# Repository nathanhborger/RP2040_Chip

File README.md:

# Palette_Chip
All information containing the mini break-out board designed for the RP2040 microcontroller.

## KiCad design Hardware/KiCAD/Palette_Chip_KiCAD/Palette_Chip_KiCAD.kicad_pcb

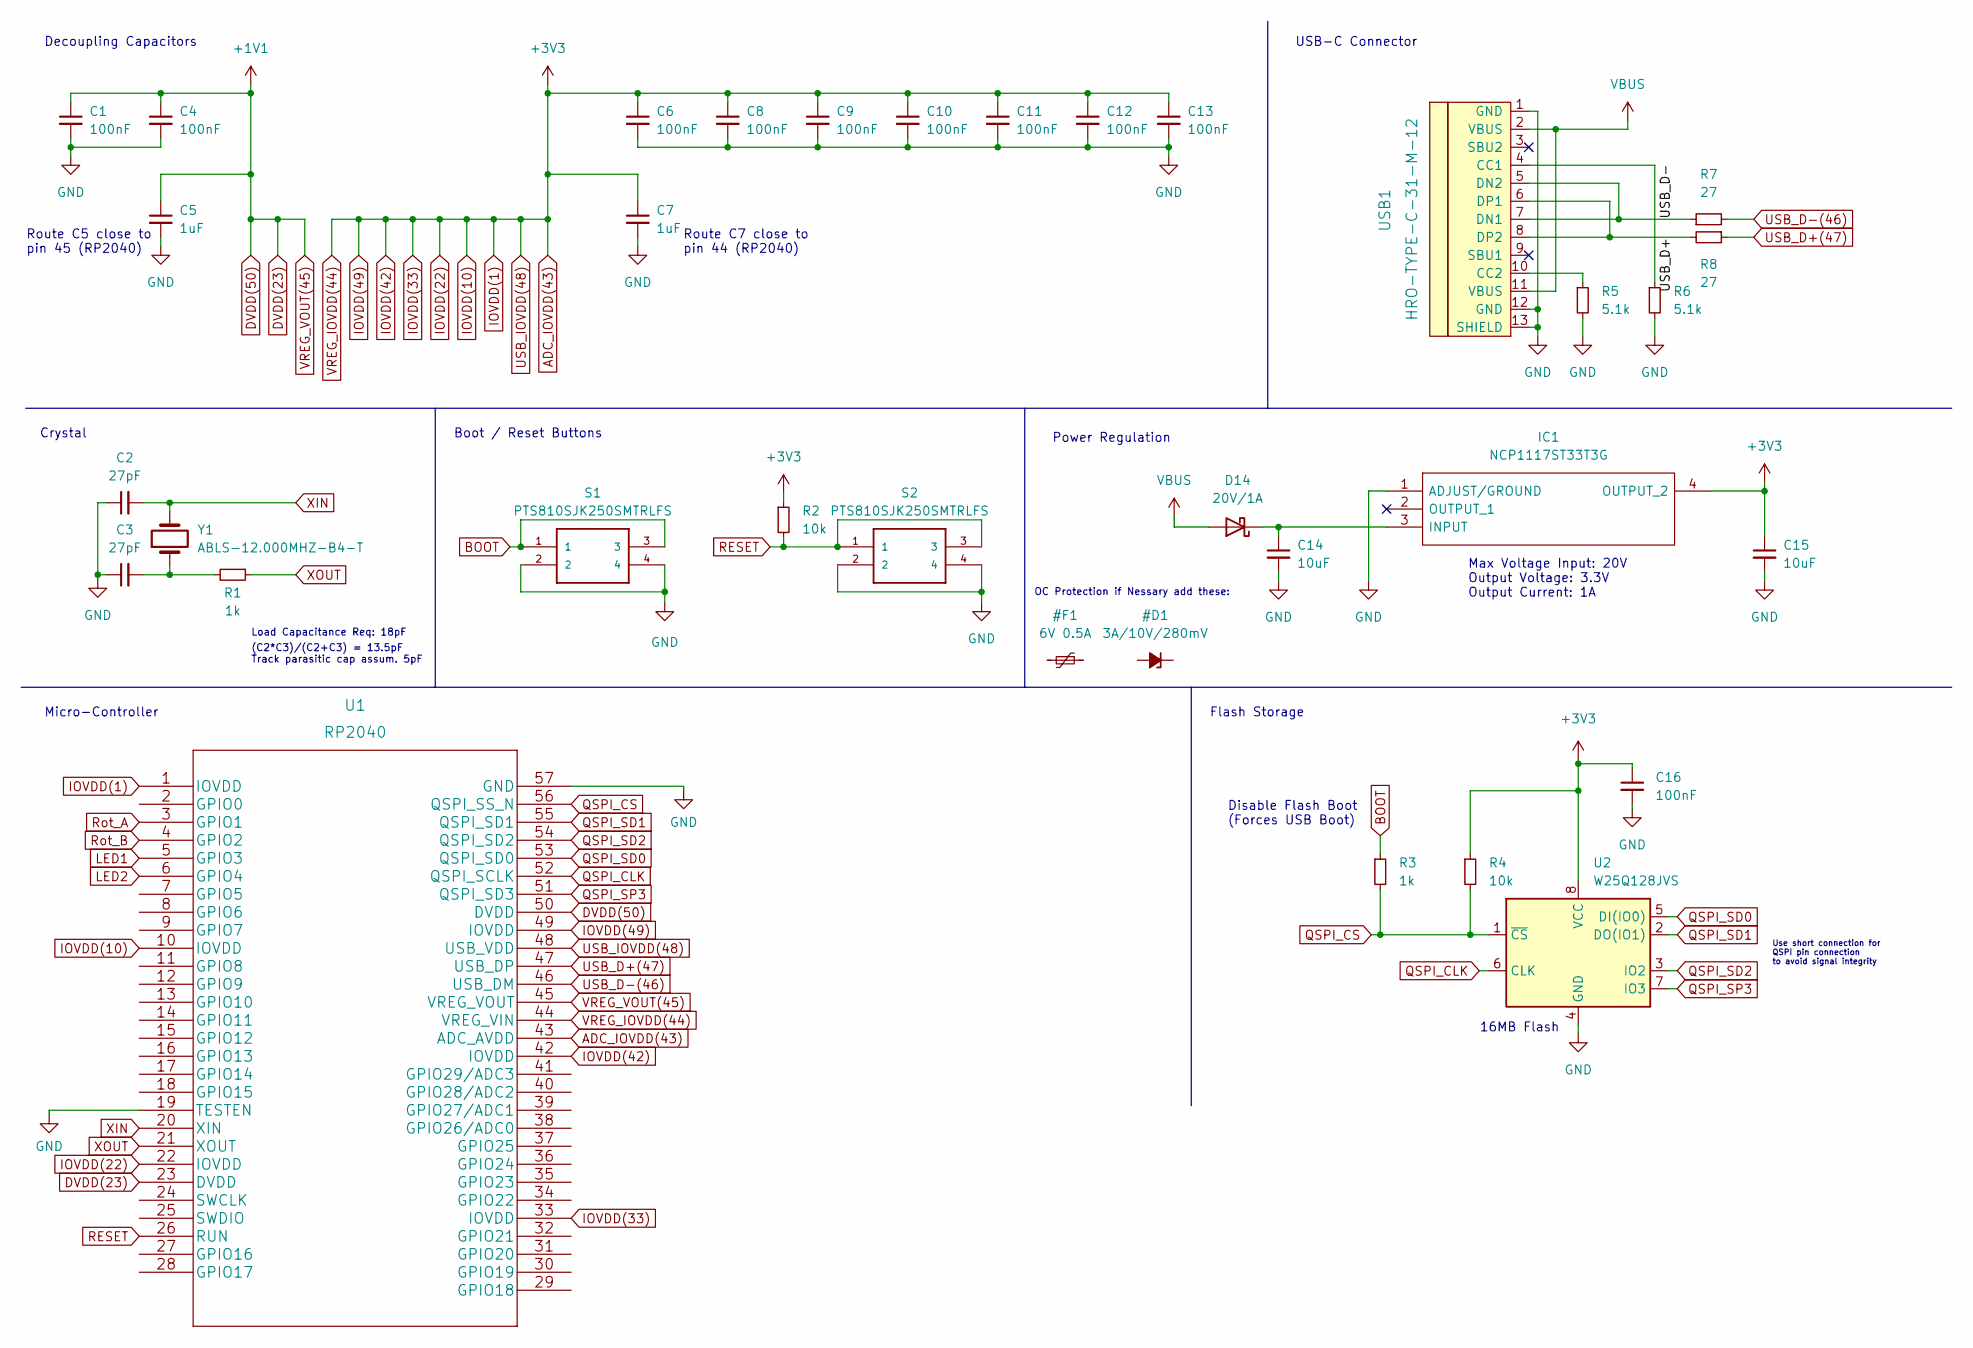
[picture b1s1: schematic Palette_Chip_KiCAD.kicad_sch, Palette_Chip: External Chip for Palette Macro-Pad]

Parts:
C1, C4, C6, C8, C9, C10, C11, C12, C13, C16: 100nF; C_0402_1005Metric
C2, C3: 27pF; C_0402_1005Metric
C5, C7: 1uF; C_0402_1005Metric
C14, C15: 10uF; C_0402_1005Metric
D14: 20V/1A; D_SOD-123F
IC1: NCP1117ST33T3G; SOT230P700X180-4N; Mouser Part Number 863-NCP1117ST33T3G
R1, R3: 1k; R_0402_1005Metric
R2, R4: 10k; R_0402_1005Metric
R5, R6: 5.1k; R_0402_1005Metric
R7, R8: 27; R_0402_1005Metric
S1, S2: PTS810SJK250SMTRLFS; PTS810SJG250SMTRLFS; MANUFACTURER_PART_NUMBER PTS810SJK250SMTRLFS
U1: RP2040; RP2040-QFN-56
U2: W25Q128JVS; SOIC-8_5.23x5.23mm_P1.27mm
USB1: HRO-TYPE-C-31-M-12; HRO-TYPE-C-31-M-12-Assembly
Y1: ABLS-12.000MHZ-B4-T; 445I23D12M00000

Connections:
/USB_D+: R8.2, USB1.6 (DP1), USB1.8 (DP2)
/USB_D-: R7.1, USB1.5 (DN2), USB1.7 (DN1)
ADC_IOVDD(43): C6.1, C7.1, C8.1, C9.1, C10.1, C11.1, C12.1, C13.1, C15.1, C16.1, IC1.4 (OUTPUT_2), R2.1, R4.1, U1.1 (IOVDD), U1.10 (IOVDD), U1.22 (IOVDD), U1.33 (IOVDD), U1.42 (IOVDD), U1.43 (ADC_AVDD), U1.44 (VREG_VIN), U1.48 (USB_VDD), U1.49 (IOVDD), U2.8 (VCC)
BOOT: R3.1, S1.1, S1.3
DVDD(23): C1.1, C4.1, C5.1, U1.23 (DVDD), U1.45 (VREG_VOUT), U1.50 (DVDD)
GND: C1.2, C2.1, C3.1, C4.2, C5.2, C6.2, C7.2, C8.2, C9.2, C10.2, C11.2, C12.2, C13.2, C14.2, C15.2, C16.2, IC1.1 (ADJUST/GROUND), R5.2, R6.2, S1.2, S1.4, S2.2, S2.4, U1.19 (TESTEN), U1.57 (GND), U2.4 (GND), USB1.1 (GND), USB1.12 (GND), USB1.13 (SHIELD)
LED1: U1.5 (GPIO3); also elsewhere on the board
LED2: U1.6 (GPIO4); also elsewhere on the board
unnamed: C3.2, R1.2, Y1.1
unnamed: C14.1, D14.1 (K), IC1.3 (INPUT)
unnamed: R5.1, USB1.10 (CC2)
unnamed: R6.1, USB1.4 (CC1)
QSPI_CLK: U1.52 (QSPI_SCLK), U2.6 (CLK)
QSPI_CS: R3.2, R4.2, U1.56 (QSPI_SS_N), U2.1 (~CS)
QSPI_SD0: U1.53 (QSPI_SD0), U2.5 (DI(IO0))
QSPI_SD1: U1.55 (QSPI_SD1), U2.2 (DO(IO1))
QSPI_SD2: U1.54 (QSPI_SD2), U2.3 (IO2)
QSPI_SP3: U1.51 (QSPI_SD3), U2.7 (IO3)
RESET: R2.2, S2.1, S2.3, U1.26 (RUN)
Rot_A: U1.3 (GPIO1); also elsewhere on the board
Rot_B: U1.4 (GPIO2); also elsewhere on the board
USB_D+(47): R8.1, U1.47 (USB_DP)
USB_D-(46): R7.2, U1.46 (USB_DM)
VBUS: D14.2 (A), USB1.2 (VBUS), USB1.11 (VBUS)
XIN: C2.2, U1.20 (XIN), Y1.2
XOUT: R1.1, U1.21 (XOUT)

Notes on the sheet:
16MB Flash
Disable Flash Boot (Forces USB Boot)
(C2*C3)/(C2+C3) = 13.5pF Track parasitic cap assum. 5pF
Flash Storage
Crystal
Boot / Reset Buttons
USB-C Connector
Max Voltage Input: 20V Output Voltage: 3.3V Output Current: 1A
Route C7 close to pin 44 (RP2040)
OC Protection if Nessary add these:
Decoupling Capacitors
Route C5 close to pin 45 (RP2040)
Micro-Controller
Power Regulation
Use short connection for QSPI pin connection to avoid signal integrity
Load Capacitance Req: 18pF

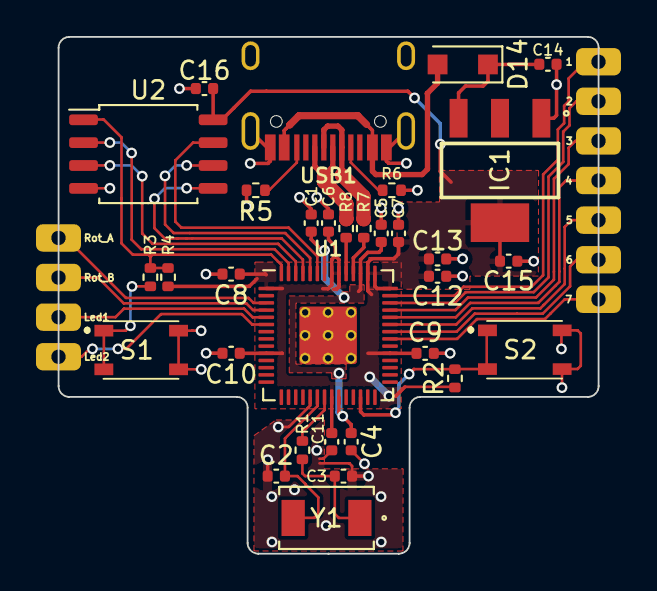
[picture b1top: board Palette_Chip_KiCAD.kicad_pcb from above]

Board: 2 copper layers, 30.0 x 28.7 mm, 43 parts (0 on the bottom side), 26 nets.

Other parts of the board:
1, 2, 3, 4, 5, 6, 7: Castellated_Pin
Led1, Led2: Castellated_Pin
Rot_A: Castellated_Pin
Rot_B: Castellated_Pin

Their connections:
LED1: Led1.1; also elsewhere on the board
LED2: Led2.1; also elsewhere on the board
Rot_A: Rot_A.1; also elsewhere on the board
Rot_B: Rot_B.1; also elsewhere on the board

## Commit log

2023-09-14 Transfered information over from organization

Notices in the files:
parts and their libraries:
Copyright 2021 Accelerated Designs. All rights reserved.
